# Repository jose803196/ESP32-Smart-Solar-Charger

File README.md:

<!DOCTYPE html>
<html lang="en">
<head>
    <meta charset="UTF-8">
</head>
<body>
    <h1 align="center">ESP32 Smart Solar Charger System</h1>
    <p align="center">
      <em>A complete design and simulation of a solar-powered charging system for Li-ion batteries with current control and protection, managed by an ESP32.</em>
    </p>
    <hr>
    <h2>Project Overview</h2>
    <p>
        This repository contains the complete design, theoretical analysis, and simulation of a smart solar charging system. The project's goal is to efficiently capture energy from a solar panel, store it in a 18650 Li-ion battery, and provide a protected output for various loads. The core of the control logic is managed by an ESP32 microcontroller, which monitors the charging process and protects the battery from overcurrent.
    </p>
    <p>
        The development process includes theoretical calculations, circuit simulation in <strong>NGSPICE</strong>, and is intended to be followed by schematic and PCB design using <strong>KiCad</strong>.
    </p>
    <h2>System Architecture</h2>
    <p>The system is composed of the following interconnected modules, as shown in the block diagram:</p>
    
    <ol>
        <li><strong>Solar Panel:</strong> Captures solar energy and converts it into electrical energy.</li>
        <li><strong>DC-DC Buck Converter:</strong> Steps down the voltage from the solar panel to a suitable level for charging the battery.</li>
        <li><strong>Current Sensor:</strong> A shunt resistor measures the charging current in real-time.</li>
        <li><strong>ESP32 Microcontroller:</strong> Acts as the brain of the system. It reads the current sensor and controls a switch (MOSFET) to protect the battery from overcurrent.</li>
        <li><strong>18650 Battery:</strong> Stores the energy.</li>
        <li><strong>Load:</strong> The device(s) that will consume the stored energy.</li>
    </ol>
    <h2>Technical Details & Theoretical Framework</h2>
    <h3>1. Solar Panel Model</h3>
    <p>A double-diode model is used for theoretical calculations and simulation, representing the photocurrent (I_ph), series resistance (Rs), and parallel resistance (Rp). For a <strong>RNG-100D</strong> panel, the parameters were calculated as:</p>
    <ul>
        <li><code>Rp = 30 Ω</code></li>
        <li><code>Rs = 0.6805 Ω</code></li>
    </ul>
    <h3>2. Buck Converter Design</h3>
    <p>The Buck converter is designed to step down the panel's voltage (assumed ~12V) to the battery's charging voltage (~4.25V). The key design parameters for a 50 kHz switching frequency are:</p>
    <ul>
        <li><strong>Duty Cycle (D):</strong> 0.3542</li>
        <li><strong>Inductor (L):</strong> > 52.79 µH (A 300 µH inductor was chosen)</li>
        <li><strong>Capacitor (C):</strong> > 61.12 µF</li>
    </ul>
    <h3>3. Current Sensing and Protection</h3>
    <p>A <strong>0.05 Ω shunt resistor</strong> is placed in series with the battery. The ESP32 measures the voltage drop across this resistor.</p>
    <ul>
        <li>The protection logic is triggered if the current exceeds <strong>5A</strong>.</li>
        <li>This corresponds to a shunt voltage of: <code>V_shunt = 5A * 0.05Ω = 0.25V</code>.</li>
        <li>If <code>V_shunt > 0.25V</code>, the ESP32 sends a signal to open a MOSFET switch, disconnecting the load to protect the battery.</li>
    </ul>
    <h2>Simulation</h2>
    <p>The entire circuit was simulated using NGSPICE to verify the theoretical design. The simulation uses a PWL (Piecewise Linear) source to model voltage variations from the solar panel.</p>
    <h4>NGSPICE Simulation Code</h4>
    <pre><code>
* Battery charging system with current control 
* Electronic Equipment Design 
* Student: Jose Lopez

********** Solar Panel (I-V and Power Curve)  
Iph 0 1 DC 5        ; Current source (photocurrent)  
D1 1 0 D            ; Diode  
D2 1 0 D            ; Diode  
Rs 1 2 0.6805       ; Series resistance  
Rp 1 0 30           ; Parallel resistance  

********** Buck Converter  
Vpanel 2 0 AC PWL(0 0 100u 12 300u 90 500u 80 700u 70 900u 12)    ; Solar panel output voltage (node 2)

* For the switch
Vsin onda 0 AC sin(0 6 50k)

S1 2 SW onda 0 SW_MOD ; Switch
D3 0 SW D1N4148       ; Freewheeling diode
L1 SW OUT 300uH       ; Inductor  
C1 OUT 0 61uF         ; Output capacitor  

********** Shunt resistor (Current sensor)
Rshunt OUT BAT 0.05   ; 0.05 Ω shunt

********** 18650 Battery (simplified model)
Vbat BAT 0 DC 4.2             ; Nominal cell voltage (3.7 V), I'll use 4.2 for theoretical calculations
Rinternal BAT BAT_int 0.1     ; Internal resistance (100 mΩ)
C_soc BAT_int 0 3000F IC=3.7  ; Capacitor to simulate SOC (3000F = ~2500 mAh)

********** ESP32 (Comparator + Control)
Vref control_ref 0 DC 0.25  
Bcontrol control_signal 0 V=V(OUT,BAT) > V(control_ref) ? 0 : 5
S_control BAT_int LOAD control_signal 0 SW_MODD ; Control MOSFET

* Loads
Rload LOAD 0 10       ; Main load
Rphone LOAD 0 20      ; Additional phone charger

* Parameters
.model SW_MOD SW (ROFF=1E+12 RON=1 VT=2 VH=0.2)
.model D D(Is=1e-9, N=1, Bv=100, Ibv=1e-9, Cjo=1e-12)  
.model D1N4148 D(Is=1e-9 N=1 vt=0.7)
.model SW_MODD SW(ROFF=1E+12 RON=1 VT=2.5 VH=0.5)  ; Realistic MOSFET

.control
  tran 0.1u 3m UIC
  set filetype=ascii  
  run
  plot  v(2) v(OUT) v(BAT_int) ylabel "Panel, Buck and Battery"
  plot (v(OUT,BAT)/0.05) ylabel "Current (A)" 
  plot v(LOAD) ylabel "ESP32 control" 
.endc
.end
    </code></pre>
    <h4>Simulation Results</h4>
    <p>The plots confirm that:</p>
    <ul>
      <li>The Buck converter correctly regulates the voltage to ~4.2V.</li>
      <li>The current sensor accurately reflects the charging current.</li>
      <li>The ESP32 control logic successfully disconnects the load when the current exceeds the 5A threshold.</li>
    </ul>
    <!-- Coloca aquí las imágenes de tus simulaciones -->
    <p align="center">

    </p>
    <hr>
    <h2>How to Use</h2>
    <ol>
        <li>Clone the repository.</li>
        <li>Open the <code>.cir</code> file in a SPICE-compatible simulator like NGSPICE.</li>
        <li>Run the simulation to generate the plots.</li>
        <li>The KiCad files (schematic and PCB) will be added in a future update.</li>
    </ol>
</body>
</html>

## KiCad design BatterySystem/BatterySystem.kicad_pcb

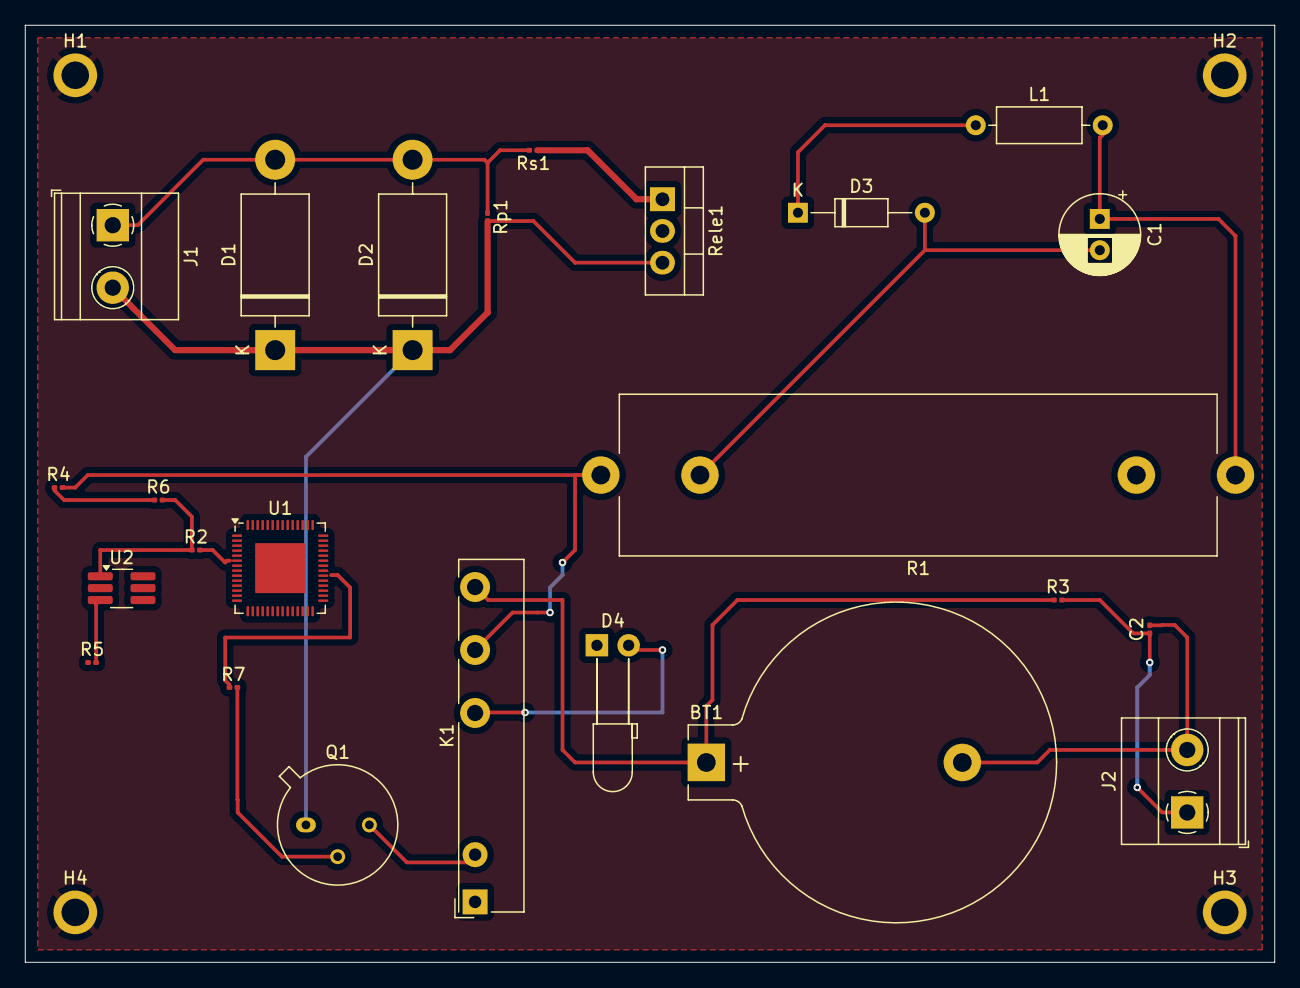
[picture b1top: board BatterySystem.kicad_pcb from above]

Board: 2 copper layers, 100.0 x 75.0 mm, 28 parts (0 on the bottom side), 19 nets.

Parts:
BT1: Battery_Cell; BatteryHolder_Keystone_104_1x23mm
C1: 61u; CP_Radial_D6.3mm_P2.50mm
C2: 3000; C_0201_0603Metric
D1, D2: 1N5408; D_DO-201AD_P15.24mm_Horizontal
D3: 1N4148; D_DO-35_SOD27_P10.16mm_Horizontal
D4: LED; LED_D3.0mm_Horizontal_O6.35mm_Z10.0mm
H1, H2, H3, H4: MountingHole_2.2mm_M2_ISO7380_Pad
J1, J2: Screw_Terminal_01x02; TerminalBlock_Phoenix_MKDS-1,5-2_1x02_P5.00mm_Horizontal
K1: Fujitsu_FTR-LYCA005x; Relay_SPDT_Fujitsu_FTR-LYCA005x_FormC_Vertical
L1: 300u; L_Axial_L6.6mm_D2.7mm_P10.16mm_Horizontal_Vishay_IM-2
Q1: 2N2219; TO-39-3
R1: R_Shunt; R_Axial_Shunt_L47.6mm_W12.7mm_PS34.93mm_P50.80mm
R2: 1.0k; R_0201_0603Metric
R3: 0.1; R_0201_0603Metric
R4, R7: 1k; R_0201_0603Metric
R5: 1; R_0201_0603Metric
R6: 10k; R_0201_0603Metric
Rele1: TLP175A; TO-220-3_Vertical
Rp1: 30; R_0201_0603Metric
Rs1: 0.65; R_0201_0603Metric
U1: ESP32-S3; QFN-56-1EP_7x7mm_P0.4mm_EP4x4mm
U2: LM358; TSOT-23-6_HandSoldering

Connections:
GND: H1.1, H2.2, H3.3, H4.4
IShunt: K1.11, R1.4, R4.2
Inputsolar1: Rele1.1, Rs1.1
Inputsolar2: BT1.2 (-), C1.2, C2.2, D1.1 (K), D2.1 (K), D3.2 (A), D4.1 (K), J1.2, J2.2, Q1.1 (E), R1.3, R5.1, Rele1.3, Rp1.2, U1.57 (GND)
unnamed: C1.1, L1.2, R1.1
unnamed: D1.2 (A), D2.2 (A), J1.1, Rp1.1, Rs1.2
unnamed: D3.1 (K), L1.1
unnamed: D4.2 (A), K1.12
unnamed: C2.1, J2.1, R3.2
unnamed: Q1.2 (B), R7.2
unnamed: K1.A2, Q1.3 (C)
unnamed: R2.1, R6.2, U2.1
unnamed: R2.2, U1.6 (GPIO1)
unnamed: U1.2 (VDD3P3), U1.3 (VDD3P3)
unnamed: U1.55 (VDDA), U1.56 (VDDA)
unnamed: R5.2, U2.3 (+)
unnamed: R4.1, R6.1, U2.2 (-)
Señal: R7.1, U1.34 (SPIQ)
V^{+}: BT1.1 (+), K1.14, R3.1

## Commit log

2025-07-11 fix: Init the project and update the report
2025-07-11 fix: upload the code´s project
2025-07-11 fix: upload README file
2025-07-11 fix: update title in README file
